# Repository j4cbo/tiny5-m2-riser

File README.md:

# Tiny5 M.2 Riser

This is a project I've been working on to create a custom riser board for Lenovo Tiny5
series (M920q/M920x/P330 Tiny) to support an additional two M.2 SSDs as well as a 10G Ethernet card.
It builds on badger707's excellent work investigating [PCIe bifurcation](https://github.com/badger707/m920q-pcie-bifurcation/)
and adding a [second M.2 slot](https://github.com/badger707/m920q-dual-NVME/) to these systems.

Fully loaded with this riser, an M920x can support four M.2 2280 M-key SSDs, as well as an additional PCI card,
a SATA boot SSD, and an M.2 2230 E-key module. It also provides a standard 12 volt fan header.

This works **only** with the M920q, M920x, and P330 Tiny. Other systems in the Tiny5 family do not support PCIe bifurcation.

Block diagram:

According to the IQ3X0IL board schematics, the system +3V3 rail is rated for 9.74 amps, and is used for
various onboard components as well. A typical M.2 SSD is specified for 2.5 to 3.0 amps so four of them at
full load could exceed the power supply capacity. The riser board therefore uses a buck converter from
the +12V rail to avoid overloading the system +3V3 supply.

In addition to the power supply and clock buffer, a custom-programmed GreenPAK is used to handle
power sequencing and ancillary PCIe signals like PERST# and CLKREQ#.

As of 5/14/2024, I have a production batch of these and am now selling them, see issue #1.

Using this **requires soldering** two 0402 resistors on the motherboard to enable PCIe bifurcation.

## Mounting Bracket

There is also a mounting bracket to hold the additional M.2 drives in place. It replaces the WiFi antenna
support at the front of the case.

## Disclaimer

This design is EXPERIMENTAL and provided WITHOUT WARRANTY. It has not been approved by Lenovo, the
FCC, or really anybody. I am not responsible if it breaks your computer, deletes your data, burns
down your house, or kicks your cat.

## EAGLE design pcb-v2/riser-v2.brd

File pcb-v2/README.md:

# Ordering Boards

The riser can be assembled by any PCB manufacturing contractor. I used [JLCPCB](https://jlcpcb.com/) and have optimized the parts list for their process. To order your own batch:

- Log in to your account (or create a new one, if you don't already have one).
- Upload `riser-v2.zip` with the "Add gerber file" box on the home page.
- Some properties of the PCB (4 layers, outside dimensions) will be auto-detected, but you will need to change several options:
  - Surface Finish: **ENIG**
  - Layer Stackup: **JLC04161H-7628** (this is critical for the PCIe bus to work!)
  - Impedance Control: **Yes**
    - Select +-10% option (Excel template is included in Gerber zip)
  - Mark on PCB: **Order Number (Specify Position)**
  - Gold Fingers: **Yes**
  - 30° finger chamfered: **No** 
- Check the "PCB Assembly" box and make sure these options are selected:
  - PCBA Type: **Standard** (Economic not available)
  - Assembly Side: **Top Side**
  - Edge Rails/Fiducials: **Added by JLCPCB**
  - Parts Selection: **By Customer**
  - PCBA Qty: although JLC will manufacture PCBs only in multiples of 5, you can choose to have them solder parts onto as few as 2 of them - but doing so usually doesn't save much money.
- Click "Next". Make sure the top side of the PCB is selected, and click "Next" again.
- Upload `riser-v2_top_bom.csv` and `riser-v2_top_cpl.csv`.
- At this point you should see a parts list showing which parts are in stock and which are out of stock. Most likely, the `SI53152-A01AGMR` clock buffer chip and `MDT350M01001VT` right-angle M.2 connector will be out of stock, so you'll need to use JLCPCB's global sourcing tool to order them. If any other parts are out of stock, note those as well.
- If parts are out of stock, you can click "next", choose "Do not place", and "next" again to see what the cost would be excluding the missing parts. Don't actually check out with missing parts, unless you're willing to buy and solder them yourself. If you're just getting an estimate, don't worry about the component placements being just right.
- Go to the [JLCPCB Parts Manager](https://jlcpcb.com/user-center/smtPrivateLibrary/myPartsLib) and click "Global Sourcing Parts".
  - For the clock buffer, search for either `SI53152-A01AGM` or `SI53152-A01AGMR` (these are equivalent parts). Find a supplier with an MOQ (minumum order quantity) less than the number of risers you're making and click "add".
  - Repeat for any other out-of-stock parts.
- Click "Parts Cart" on the left-hand sidebar and make sure "Global Sourcing Parts" near the top is selected. You should see the parts you added. Then check out. What you are doing in this step is paying JLCPCB to source and store those parts for your future order. It usually takes a few weeks for them to arrive, and you'll get an email when that happens.
- Once the parts you ordered are available, repeat the whole process from the top. **Make sure to choose the right Impedance Control and Layer Stackup options if you're starting over.**
- At the "Component Placements" step, click "Select all top parts" and use the arrow keys to move the parts so that they line up with the pads on the board. You can rotate parts 90 degrees at a time with the spacebar.
  - All the R, C, and L parts are symmetric - there's no such thing as the wrong way around.
  - The pins of J4 should be sticking off in space past the end of the board, away from all the other components.
  - Make sure the white circle on IC1 and IC2 is near the corresponding white circle on the PCB.
  - The "out" pin of Y1 should be on the top left side, near the white "Y1" text on the PCB.
  - The + side of D1 should be down towards the PCIe slot.
- Finally, click "save to cart" and check out.

If you use another manufacturer, give them the following PCB specifications:
- Controlled impedance
- Coplanar differential pair (on L1 referenced to L2, and on L4 referenced to L3) of 85 ohms nominal, +/- 10 ohms
- ENIG surface finish with gold fingers
- No chamfer

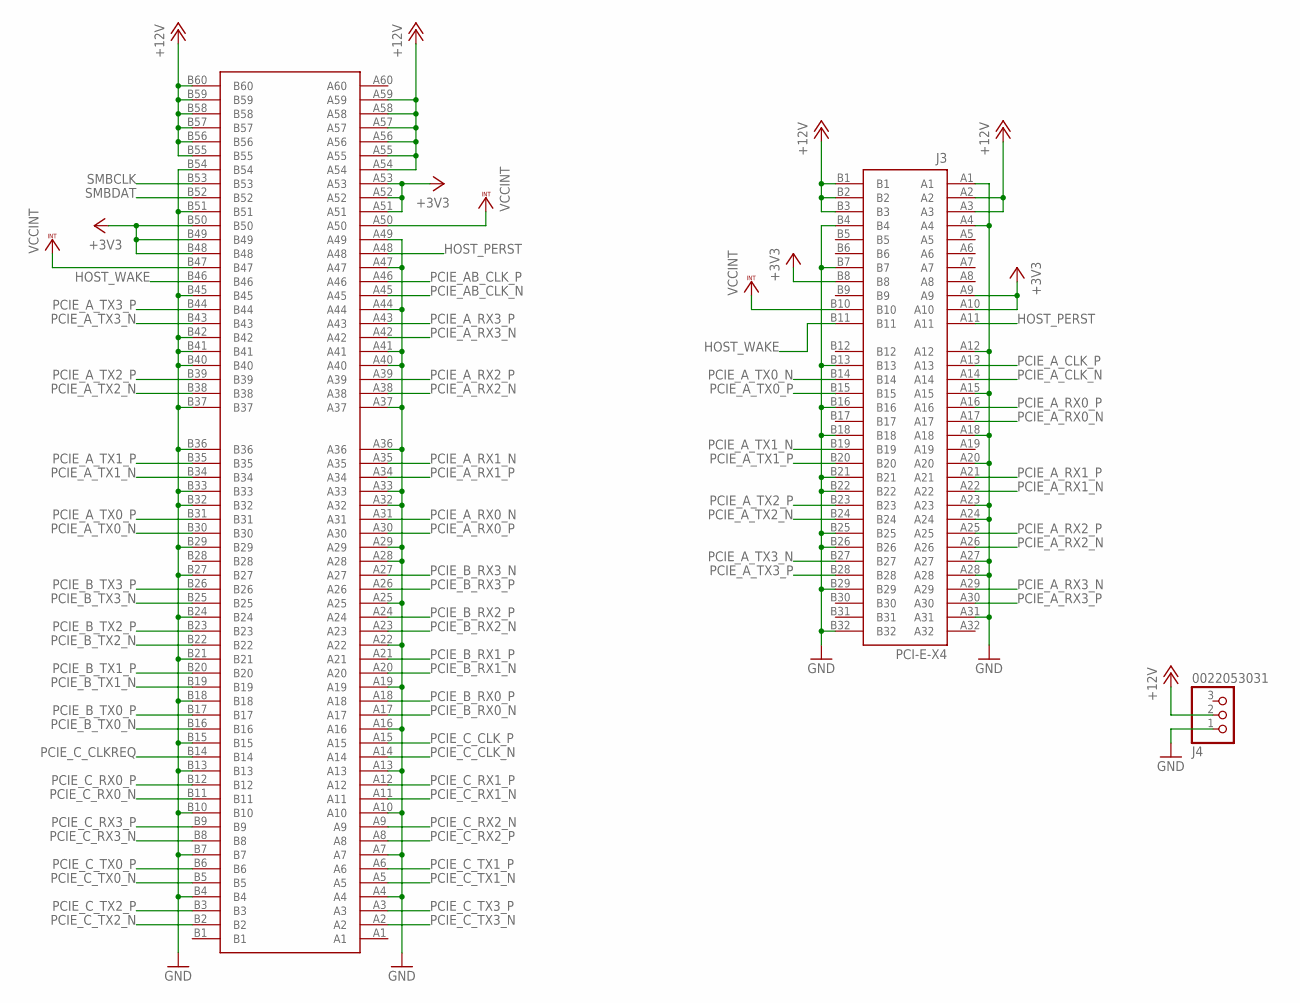
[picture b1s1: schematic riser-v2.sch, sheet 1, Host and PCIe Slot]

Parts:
J3: PCI-E-X4
J4: 0022053031; 1X03
JP1: ADDR0262; ADDR0262-EDGE

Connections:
+3V3: J3.A9, J3.A10, J3.B8, JP1.A51, JP1.A52, JP1.A53, JP1.B48, JP1.B49, JP1.B50; also elsewhere on the board
+12V: J3.A2, J3.A3, J3.B1, J3.B2, J3.B3, J4.2, JP1.A54, JP1.A55, JP1.A56, JP1.A57, JP1.A58, JP1.A59, JP1.B55, JP1.B56, JP1.B57, JP1.B58, JP1.B59, JP1.B60; also elsewhere on the board
GND: J3.A1, J3.A4, J3.A12, J3.A15, J3.A18, J3.A20, J3.A23, J3.A24, J3.A27, J3.A28, J3.A31, J3.B4, J3.B7, J3.B13, J3.B16, J3.B18, J3.B21, J3.B22, J3.B25, J3.B26, J3.B29, J3.B32, J4.1, JP1.A4, JP1.A7, JP1.A10, JP1.A13, JP1.A16, JP1.A19, JP1.A22, JP1.A25, JP1.A28, JP1.A29, JP1.A32, JP1.A33, JP1.A36, JP1.A37, JP1.A40, JP1.A41, JP1.A44, JP1.A47, JP1.A49, JP1.B4, JP1.B7, JP1.B10, JP1.B13, JP1.B15, JP1.B18, JP1.B21, JP1.B24, JP1.B27, JP1.B29, JP1.B32, JP1.B33, JP1.B36, JP1.B37, JP1.B40, JP1.B41, JP1.B42, JP1.B45, JP1.B51, JP1.B54; also elsewhere on the board
HOST_PERST: J3.A11, JP1.A48; also elsewhere on the board
HOST_WAKE: J3.B11, JP1.B46; also elsewhere on the board
PCIE_AB_CLK_N: JP1.A45; also elsewhere on the board
PCIE_AB_CLK_P: JP1.A46; also elsewhere on the board
PCIE_A_CLK_N: J3.A14; also elsewhere on the board
PCIE_A_CLK_P: J3.A13; also elsewhere on the board
PCIE_A_RX0_N: J3.A17, JP1.A31
PCIE_A_RX0_P: J3.A16, JP1.A30
PCIE_A_RX1_N: J3.A22, JP1.A35
PCIE_A_RX1_P: J3.A21, JP1.A34
PCIE_A_RX2_N: J3.A26, JP1.A38
PCIE_A_RX2_P: J3.A25, JP1.A39
PCIE_A_RX3_N: J3.A29, JP1.A42
PCIE_A_RX3_P: J3.A30, JP1.A43
PCIE_A_TX0_N: J3.B14, JP1.B30
PCIE_A_TX0_P: J3.B15, JP1.B31
PCIE_A_TX1_N: J3.B19, JP1.B34
PCIE_A_TX1_P: J3.B20, JP1.B35
PCIE_A_TX2_N: J3.B24, JP1.B38
PCIE_A_TX2_P: J3.B23, JP1.B39
PCIE_A_TX3_N: J3.B27, JP1.B43
PCIE_A_TX3_P: J3.B28, JP1.B44
PCIE_B_RX0_N: JP1.A17; also elsewhere on the board
PCIE_B_RX0_P: JP1.A18; also elsewhere on the board
PCIE_B_RX1_N: JP1.A20; also elsewhere on the board
PCIE_B_RX1_P: JP1.A21; also elsewhere on the board
PCIE_B_RX2_N: JP1.A23; also elsewhere on the board
PCIE_B_RX2_P: JP1.A24; also elsewhere on the board
PCIE_B_RX3_N: JP1.A27; also elsewhere on the board
PCIE_B_RX3_P: JP1.A26; also elsewhere on the board
PCIE_B_TX0_N: JP1.B16; also elsewhere on the board
PCIE_B_TX0_P: JP1.B17; also elsewhere on the board
PCIE_B_TX1_N: JP1.B19; also elsewhere on the board
PCIE_B_TX1_P: JP1.B20; also elsewhere on the board
PCIE_B_TX2_N: JP1.B22; also elsewhere on the board
PCIE_B_TX2_P: JP1.B23; also elsewhere on the board
PCIE_B_TX3_N: JP1.B25; also elsewhere on the board
PCIE_B_TX3_P: JP1.B26; also elsewhere on the board
PCIE_C_CLKREQ: JP1.B14; also elsewhere on the board
PCIE_C_CLK_N: JP1.A14; also elsewhere on the board
PCIE_C_CLK_P: JP1.A15; also elsewhere on the board
PCIE_C_RX0_N: JP1.B11; also elsewhere on the board
PCIE_C_RX0_P: JP1.B12; also elsewhere on the board
PCIE_C_RX1_N: JP1.A11; also elsewhere on the board
PCIE_C_RX1_P: JP1.A12; also elsewhere on the board
PCIE_C_RX2_N: JP1.A9; also elsewhere on the board
PCIE_C_RX2_P: JP1.A8; also elsewhere on the board
PCIE_C_RX3_N: JP1.B8; also elsewhere on the board
PCIE_C_RX3_P: JP1.B9; also elsewhere on the board
PCIE_C_TX0_N: JP1.B5; also elsewhere on the board
PCIE_C_TX0_P: JP1.B6; also elsewhere on the board
PCIE_C_TX1_N: JP1.A5; also elsewhere on the board
PCIE_C_TX1_P: JP1.A6; also elsewhere on the board
PCIE_C_TX2_N: JP1.B2; also elsewhere on the board
PCIE_C_TX2_P: JP1.B3; also elsewhere on the board
PCIE_C_TX3_N: JP1.A2; also elsewhere on the board
PCIE_C_TX3_P: JP1.A3; also elsewhere on the board
SMBCLK: JP1.B53; also elsewhere on the board
SMBDAT: JP1.B52; also elsewhere on the board
VCCINT: J3.B10, JP1.A50, JP1.B47; also elsewhere on the board

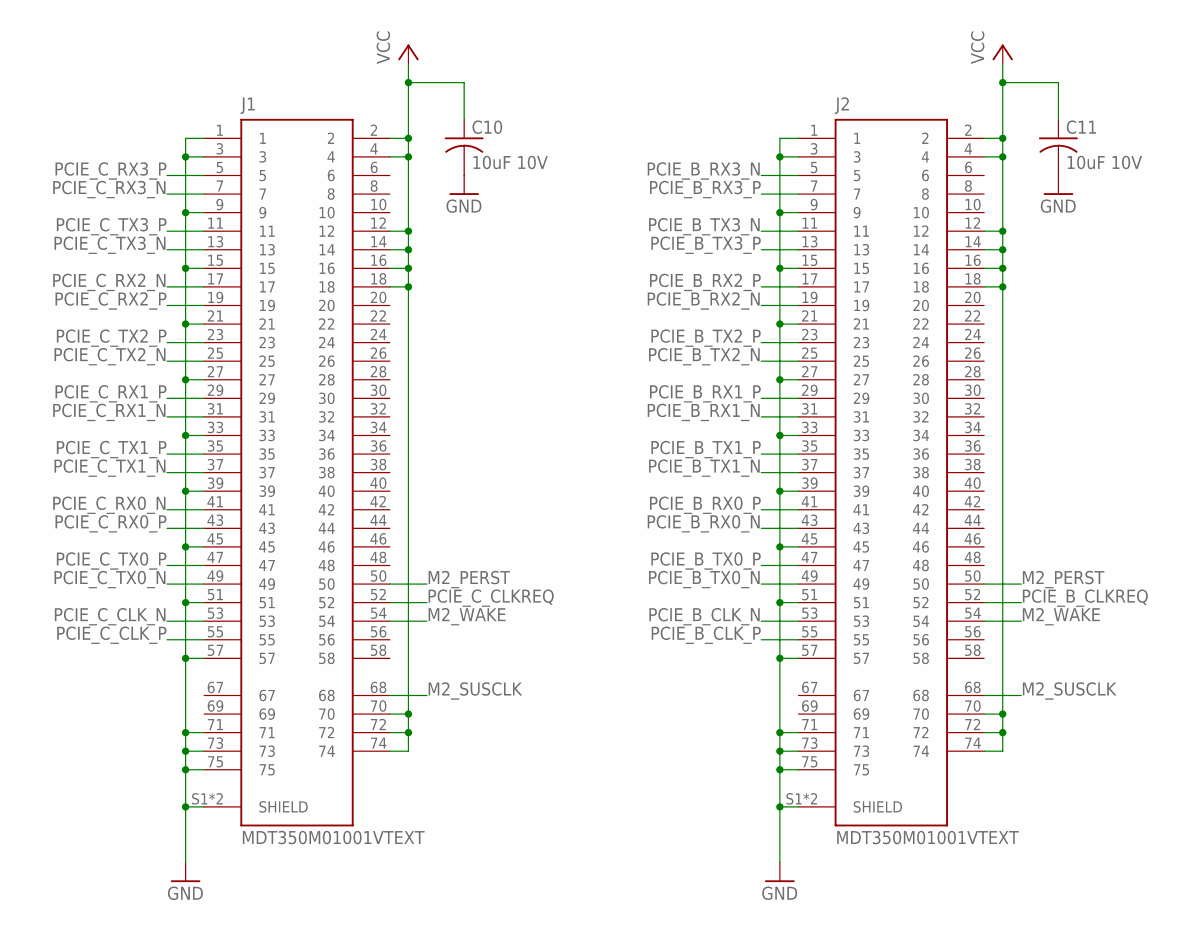
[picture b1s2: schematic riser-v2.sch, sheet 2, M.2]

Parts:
C10, C11: 10uF 10V; C0603
J1, J2: MDT350M01001VTEXT; MDT350M01001VT_EXT

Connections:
GND: C10.2, C11.2, J1.1, J1.3, J1.9, J1.15, J1.21, J1.27, J1.33, J1.39, J1.45, J1.51, J1.57, J1.71, J1.73, J1.75, J1.S1 (SHIELD), J1.S2 (SHIELD), J2.1, J2.3, J2.9, J2.15, J2.21, J2.27, J2.33, J2.39, J2.45, J2.51, J2.57, J2.71, J2.73, J2.75, J2.S1 (SHIELD), J2.S2 (SHIELD); also elsewhere on the board
M2_PERST: J1.50, J2.50; also elsewhere on the board
M2_SUSCLK: J1.68, J2.68; also elsewhere on the board
M2_WAKE: J1.54, J2.54; also elsewhere on the board
PCIE_B_CLKREQ: J2.52; also elsewhere on the board
PCIE_B_CLK_N: J2.53; also elsewhere on the board
PCIE_B_CLK_P: J2.55; also elsewhere on the board
PCIE_B_RX0_N: J2.43; also elsewhere on the board
PCIE_B_RX0_P: J2.41; also elsewhere on the board
PCIE_B_RX1_N: J2.31; also elsewhere on the board
PCIE_B_RX1_P: J2.29; also elsewhere on the board
PCIE_B_RX2_N: J2.19; also elsewhere on the board
PCIE_B_RX2_P: J2.17; also elsewhere on the board
PCIE_B_RX3_N: J2.5; also elsewhere on the board
PCIE_B_RX3_P: J2.7; also elsewhere on the board
PCIE_B_TX0_N: J2.49; also elsewhere on the board
PCIE_B_TX0_P: J2.47; also elsewhere on the board
PCIE_B_TX1_N: J2.37; also elsewhere on the board
PCIE_B_TX1_P: J2.35; also elsewhere on the board
PCIE_B_TX2_N: J2.25; also elsewhere on the board
PCIE_B_TX2_P: J2.23; also elsewhere on the board
PCIE_B_TX3_N: J2.11; also elsewhere on the board
PCIE_B_TX3_P: J2.13; also elsewhere on the board
PCIE_C_CLKREQ: J1.52; also elsewhere on the board
PCIE_C_CLK_N: J1.53; also elsewhere on the board
PCIE_C_CLK_P: J1.55; also elsewhere on the board
PCIE_C_RX0_N: J1.41; also elsewhere on the board
PCIE_C_RX0_P: J1.43; also elsewhere on the board
PCIE_C_RX1_N: J1.31; also elsewhere on the board
PCIE_C_RX1_P: J1.29; also elsewhere on the board
PCIE_C_RX2_N: J1.17; also elsewhere on the board
PCIE_C_RX2_P: J1.19; also elsewhere on the board
PCIE_C_RX3_N: J1.7; also elsewhere on the board
PCIE_C_RX3_P: J1.5; also elsewhere on the board
PCIE_C_TX0_N: J1.49; also elsewhere on the board
PCIE_C_TX0_P: J1.47; also elsewhere on the board
PCIE_C_TX1_N: J1.37; also elsewhere on the board
PCIE_C_TX1_P: J1.35; also elsewhere on the board
PCIE_C_TX2_N: J1.25; also elsewhere on the board
PCIE_C_TX2_P: J1.23; also elsewhere on the board
PCIE_C_TX3_N: J1.13; also elsewhere on the board
PCIE_C_TX3_P: J1.11; also elsewhere on the board
VCC: C10.1, C11.1, J1.2, J1.4, J1.12, J1.14, J1.16, J1.18, J1.70, J1.72, J1.74, J2.2, J2.4, J2.12, J2.14, J2.16, J2.18, J2.70, J2.72, J2.74; also elsewhere on the board

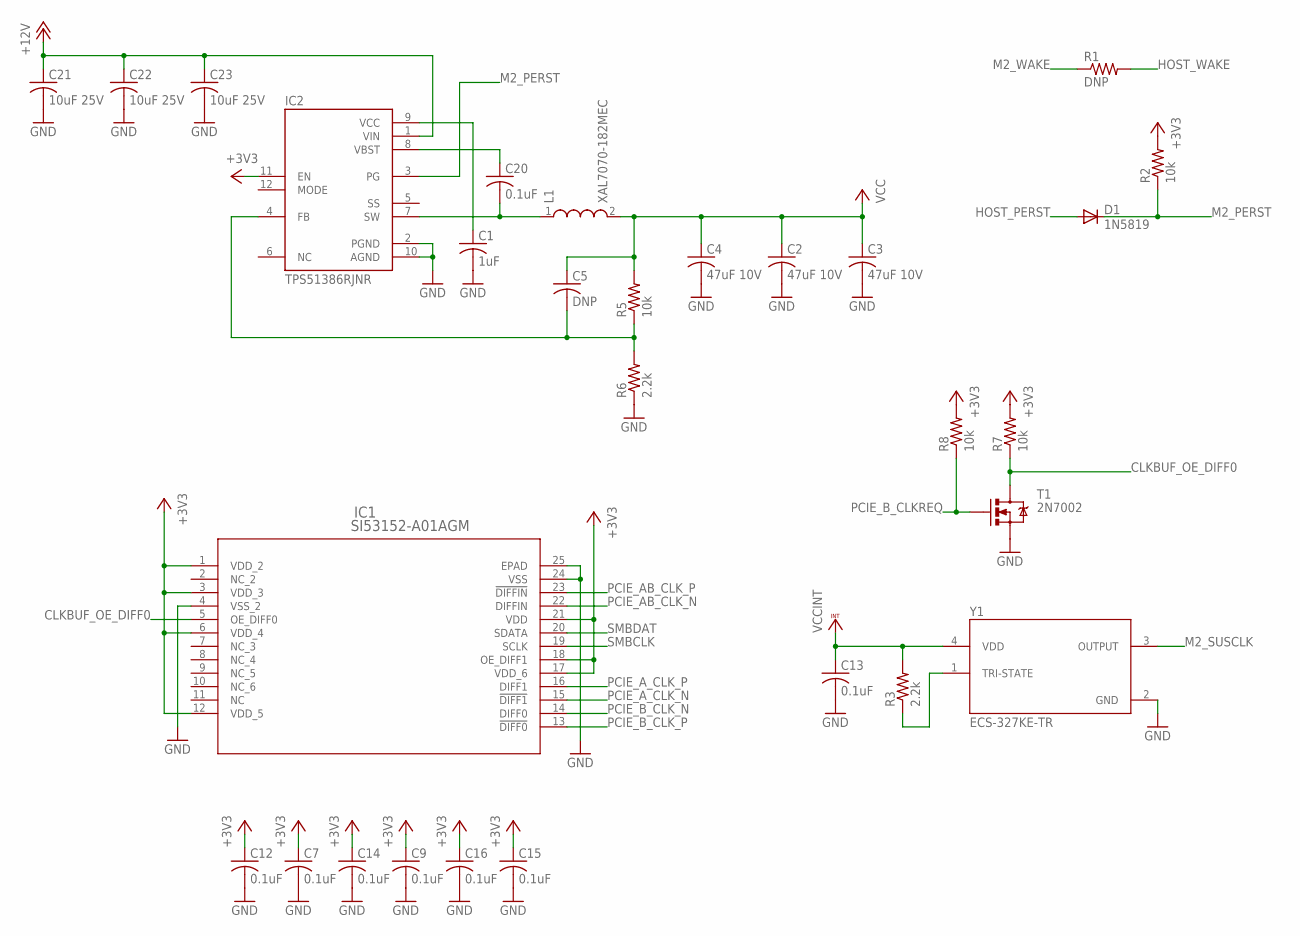
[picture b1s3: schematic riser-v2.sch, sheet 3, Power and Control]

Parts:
C1: 1uF; C0402
C2, C3, C4: 47uF 10V; C1206
C5: DNP; C0402
C7, C9, C12, C13, C14, C15, C16, C20: 0.1uF; C0402
C21, C22, C23: 10uF 25V; C1206
D1: 1N5819; SOD323-R
IC1: SI53152-A01AGM; QFN24_4X4_SIL
IC2: TPS51386RJNR; VREG_TPS51386RJNR
L1: XAL7070-182MEC; DFN750X725X700-2N; JLC_ROTATION 90
R1: DNP; R0402
R2, R5, R7, R8: 10k; R0402
R3, R6: 2.2k; R0402
T1: 2N7002; SOT23-3; JLC_ROTATION 270
Y1: ECS-327KE-TR; OSC_ECS-327KE-TR

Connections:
+3V3: C7.1, C9.1, C12.1, C14.1, C15.1, C16.1, IC1.1 (VDD_2), IC1.3 (VDD_3), IC1.6 (VDD_4), IC1.12 (VDD_5), IC1.17 (VDD_6), IC1.18 (OE_DIFF1), IC1.21 (VDD), IC2.11 (EN), R2.2, R7.2, R8.2; also elsewhere on the board
+12V: C21.1, C22.1, C23.1, IC2.1 (VIN); also elsewhere on the board
BOOT: C20.1, IC2.8 (VBST)
BUCK_VCC: C1.1, IC2.9 (VCC)
CLKBUF_OE_DIFF0: IC1.5 (OE_DIFF0), R7.1, T1.3 (D)
FB: C5.2, IC2.4 (FB), R5.1, R6.2
GND: C1.2, C2.2, C3.2, C4.2, C7.2, C9.2, C12.2, C13.2, C14.2, C15.2, C16.2, C21.2, C22.2, C23.2, IC1.4 (VSS_2), IC1.24 (VSS), IC1.25 (EPAD), IC2.2 (PGND), IC2.10 (AGND), R6.1, T1.2 (S), Y1.2 (GND); also elsewhere on the board
HOST_PERST: D1.A; also elsewhere on the board
HOST_WAKE: R1.2; also elsewhere on the board
LX: C20.2, IC2.7 (SW), L1.1
M2_PERST: D1.C, IC2.3 (PG), R2.1; also elsewhere on the board
M2_SUSCLK: Y1.3 (OUTPUT); also elsewhere on the board
M2_WAKE: R1.1; also elsewhere on the board
OSC_TRI_STATE: R3.1, Y1.1 (TRI-STATE)
PCIE_AB_CLK_N: IC1.22 (DIFFIN); also elsewhere on the board
PCIE_AB_CLK_P: IC1.23 (!DIFFIN); also elsewhere on the board
PCIE_A_CLK_N: IC1.15 (!DIFF1); also elsewhere on the board
PCIE_A_CLK_P: IC1.16 (DIFF1); also elsewhere on the board
PCIE_B_CLKREQ: R8.1, T1.1 (G); also elsewhere on the board
PCIE_B_CLK_N: IC1.14 (DIFF0); also elsewhere on the board
PCIE_B_CLK_P: IC1.13 (!DIFF0); also elsewhere on the board
SMBCLK: IC1.19 (SCLK); also elsewhere on the board
SMBDAT: IC1.20 (SDATA); also elsewhere on the board
VCC: C2.1, C3.1, C4.1, C5.1, L1.2, R5.2; also elsewhere on the board
VCCINT: C13.1, R3.2, Y1.4 (VDD); also elsewhere on the board

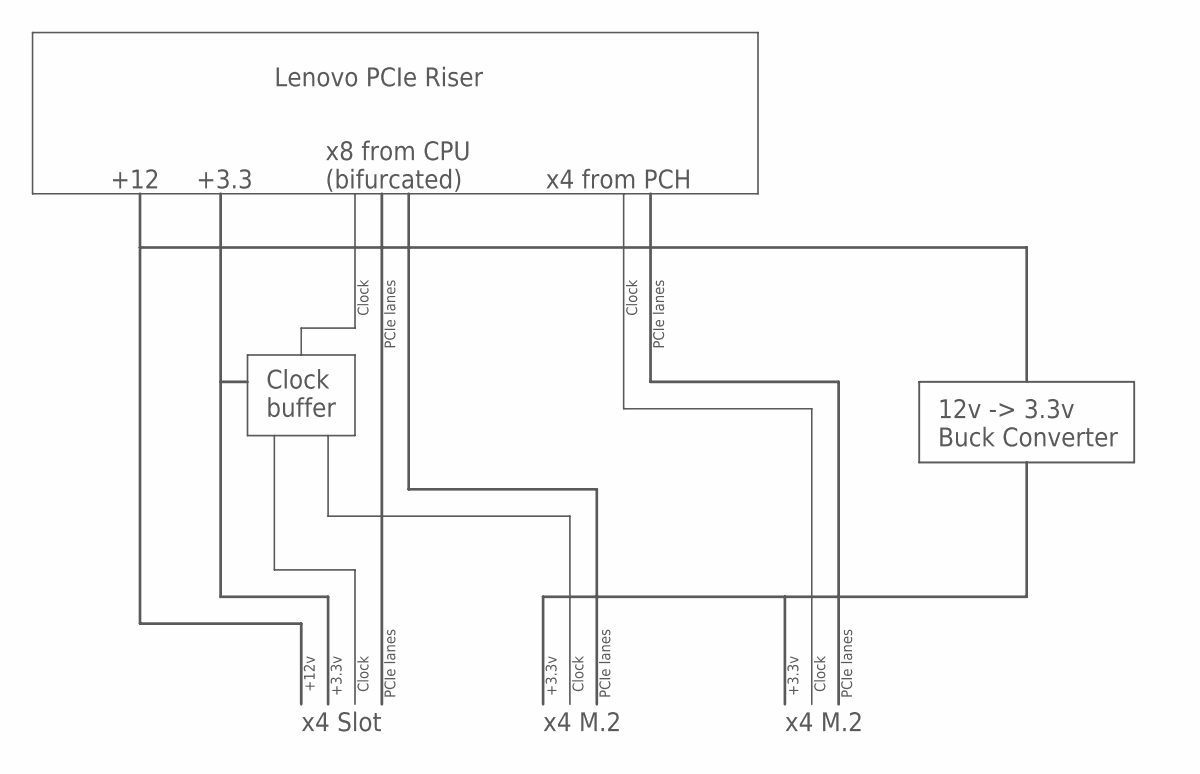
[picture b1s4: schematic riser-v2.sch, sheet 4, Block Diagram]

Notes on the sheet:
Lenovo PCIe Riser
x8 from CPU (bifurcated)
x4 from PCH
+12 +3.3
Clock buffer
x4 Slot
x4 M.2
12v -> 3.3v Buck Converter
PCIe lanes
Clock
+3.3v
+12v

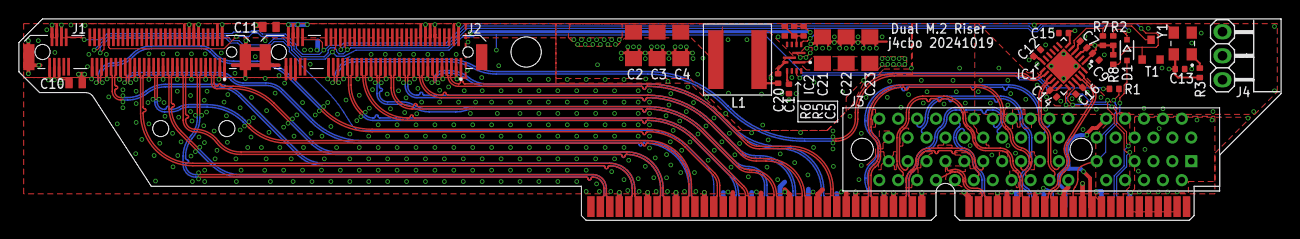
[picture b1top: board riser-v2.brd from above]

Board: 4 copper layers, 133.5 x 21.3 mm, 36 parts (0 on the bottom side), 76 nets.

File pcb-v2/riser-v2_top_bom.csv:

Comment,Designator,Footprint,LCSC Part #
0.1uF,C7 C9 C12 C13 C14 C15 C16 C20,C0402,
1N5819,D1,SOD323-R,C191023
1uF,C1,C0402,C52923
2.2k,R3 R6,R0402,C25879
2N7002,T1,SOT23-3,C8545
10k,R2 R5 R7 R8,R0402,
10uF 10V,C10,C0603,C19702
10uF 10V,C11,C0603,C19702
10uF 25V,C21 C22 C23,C1206,C13585
47uF 10V,C2 C3 C4,C1206,C96123
0022053031,J4,1X03,C706940
ECS-327KE-TR,Y1,OSC_ECS-327KE-TR,C5280579
MDT350M01001VTEXT,J1 J2,MDT350M01001VT_EXT,C722526
PCI-E-X4,J3,PCI-E-X4,C2926855
SI53152-A01AGM,IC1,QFN24_4X4_SIL,C2651396
TPS51386RJNR,IC2,VREG_TPS51386RJNR,C22388893
XAL7070-182MEC,L1,DFN750X725X700-2N,C3911679

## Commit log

2024-04-06 Add power supply info
2024-04-23 Updates; more photos
2024-04-23 new features
2024-05-14 Production boards are in
2024-05-14 Add mounting hardware
2024-05-27 Add README
2024-06-04 Add PCB files
2024-06-20 Add resistor diagram
2025-01-18 Add V2 PCB
2025-01-18 Add schematic
2025-02-27 add more mount options
2025-03-13 Do not place C5
    This was an error - see https://github.com/j4cbo/tiny5-m2-riser/issues/15
2025-03-13 Mark DNP in EAGLE files too
2025-06-01 Update README to clarify compatibility
2025-07-16 Update riser-v2_top_bom.csv
    Fixed JLPCB part numbers and removed duplicate part number for C10/C11
2025-11-03 Added impendance control Excel file and updated Gerber zip with this file
2025-11-03 Revise PCB assembly instructions in README
    Updated PCB assembly options and requirements in README.

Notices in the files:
parts and their libraries:
COPYRIGHT: Copyright (C) 2024 Ultra Librarian. All rights reserved.
